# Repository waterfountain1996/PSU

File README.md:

# PSU

A dual +/-12V power supply based on LM317 and LM337 adjustable voltage regulators.

This is my first PCB design. SMD capacitors were chosen due to me being unable to source
recommended bypass capacitors in THT footprints locally.

## Reference links

1. [LM317 Datasheet (TI)](https://www.ti.com/lit/ds/symlink/lm317.pdf)
2. [LM317 Datasheet (ONSemi)](https://www.onsemi.com/download/data-sheet/pdf/lm317-d.pdf)
3. [LM337 Datasheet (TI)](https://www.ti.com/lit/ds/symlink/lm337.pdf)
4. [LM337 Datasheet (ONSemi)](https://www.onsemi.com/download/data-sheet/pdf/lm337-d.pdf)

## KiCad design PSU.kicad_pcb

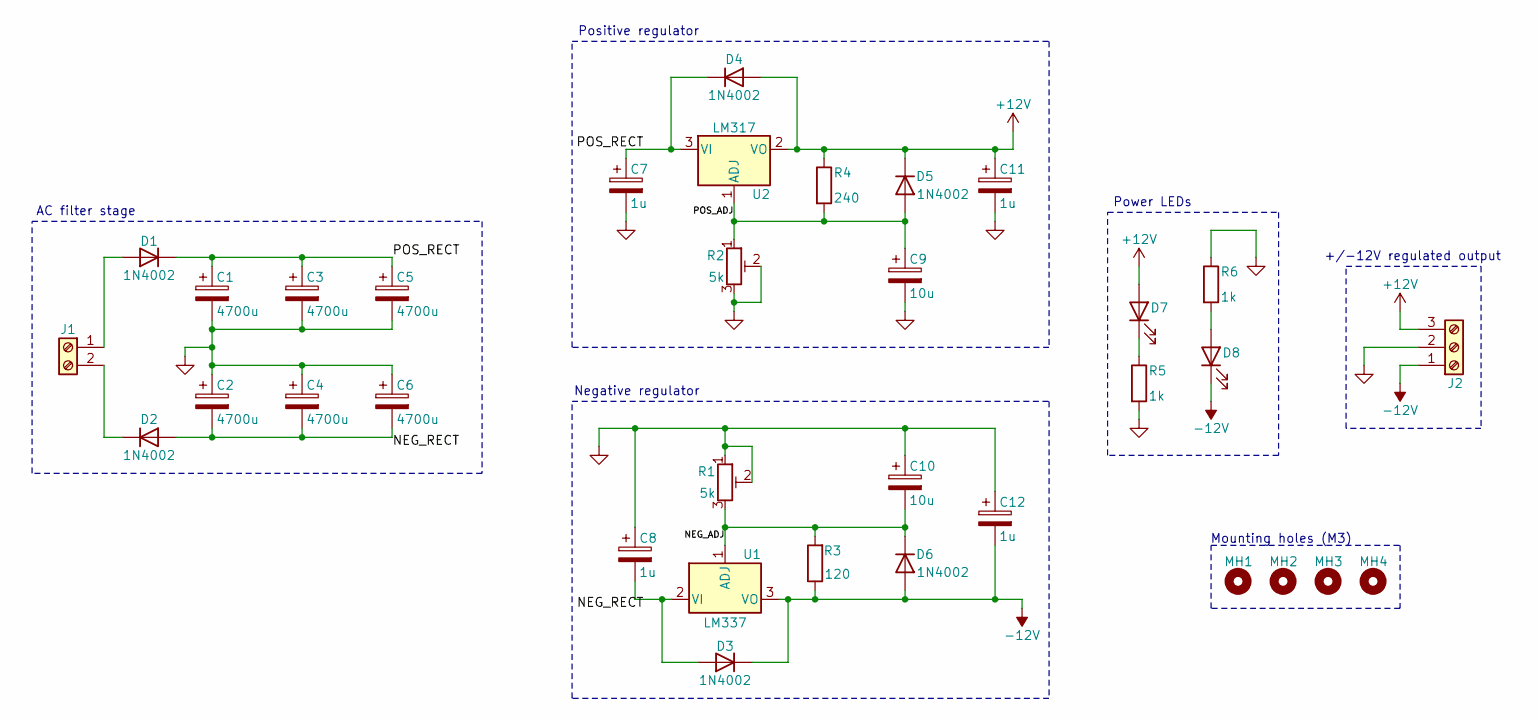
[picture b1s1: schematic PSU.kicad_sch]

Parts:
C1, C2, C3, C4, C5, C6: 4700u; CP_Radial_D16.0mm_P7.50mm
C7, C8, C11, C12: 1u; CP_EIA-3528-15_AVX-H
C9, C10: 10u; CP_EIA-3528-15_AVX-H
D1, D2, D3, D4, D5, D6: 1N4002; D_DO-41_SOD81_P7.62mm_Horizontal
D7, D8: LED; LED_D3.0mm
J1: Screw_Terminal_01x02; TerminalBlock_Phoenix_MKDS-1,5-2_1x02_P5.00mm_Horizontal
J2: Screw_Terminal_01x03; TerminalBlock_Phoenix_MKDS-1,5-3_1x03_P5.00mm_Horizontal
MH1, MH2, MH3, MH4: MountingHole; MountingHole_3.2mm_M3
R1, R2: 5k; Potentiometer_Bourns_3296W_Vertical
R3: 120; R_Axial_DIN0207_L6.3mm_D2.5mm_P7.62mm_Horizontal
R4: 240; R_Axial_DIN0207_L6.3mm_D2.5mm_P7.62mm_Horizontal
R5, R6: 1k; R_Axial_DIN0207_L6.3mm_D2.5mm_P7.62mm_Horizontal
U1: LM337; TO-220-3_Vertical
U2: LM317; TO-220-3_Vertical

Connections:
+12V: C11.1, D4.2 (A), D5.1 (K), D7.2 (A), J2.3, R4.1, U2.2 (VO)
-12V: C12.2, D3.1 (K), D6.2 (A), D8.1 (K), J2.1, R3.1, U1.3 (VO)
/NEG_ADJ: C10.2, D6.1 (K), R1.3, R3.2, U1.1 (ADJ)
/NEG_RECT: C2.2, C4.2, C6.2, C8.2, D2.2 (A), D3.2 (A), U1.2 (VI)
/POS_ADJ: C9.1, D5.2 (A), R2.1, R4.2, U2.1 (ADJ)
/POS_RECT: C1.1, C3.1, C5.1, C7.1, D1.1 (K), D4.1 (K), U2.3 (VI)
GND: C1.2, C2.1, C3.2, C4.1, C5.2, C6.1, C7.2, C8.1, C9.2, C10.1, C11.2, C12.1, J2.2, R1.1, R1.2, R2.2, R2.3, R5.2, R6.1
unnamed: D1.2 (A), J1.1
unnamed: D2.1 (K), J1.2
unnamed: D7.1 (K), R5.1
unnamed: D8.2 (A), R6.2

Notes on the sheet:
+/-12V regulated output
Positive regulator
Power LEDs
AC filter stage
Mounting holes (M3)
Negative regulator

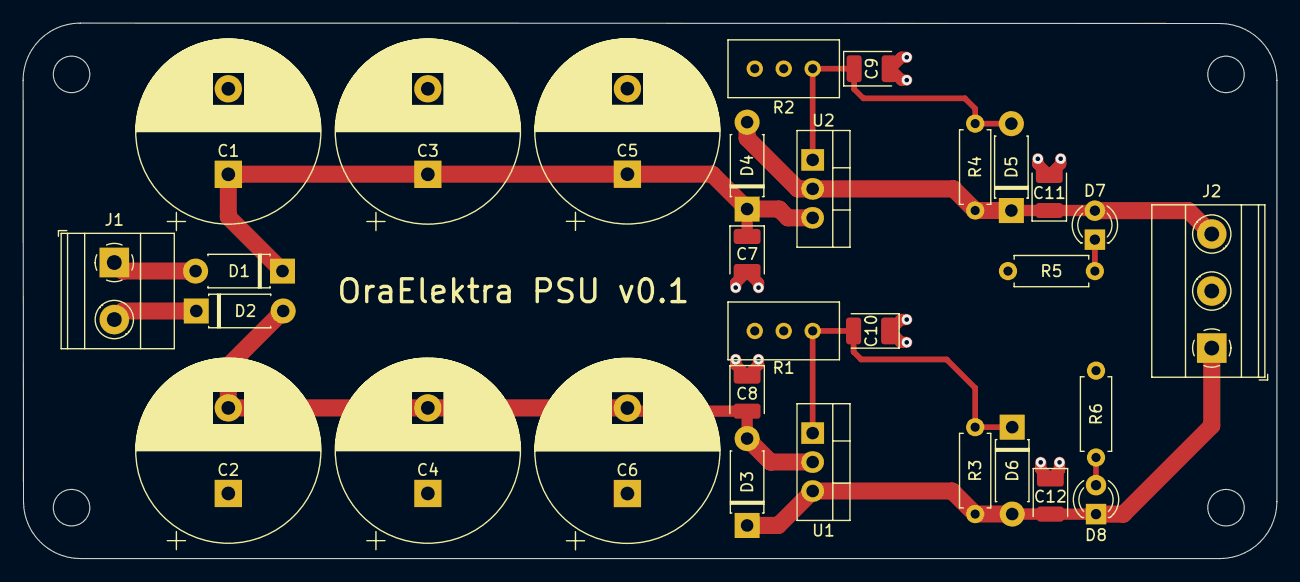
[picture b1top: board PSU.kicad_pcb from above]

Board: 2 copper layers, 110.0 x 47.0 mm, 34 parts (0 on the bottom side), 11 nets.

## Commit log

2024-05-17 Initial revision
